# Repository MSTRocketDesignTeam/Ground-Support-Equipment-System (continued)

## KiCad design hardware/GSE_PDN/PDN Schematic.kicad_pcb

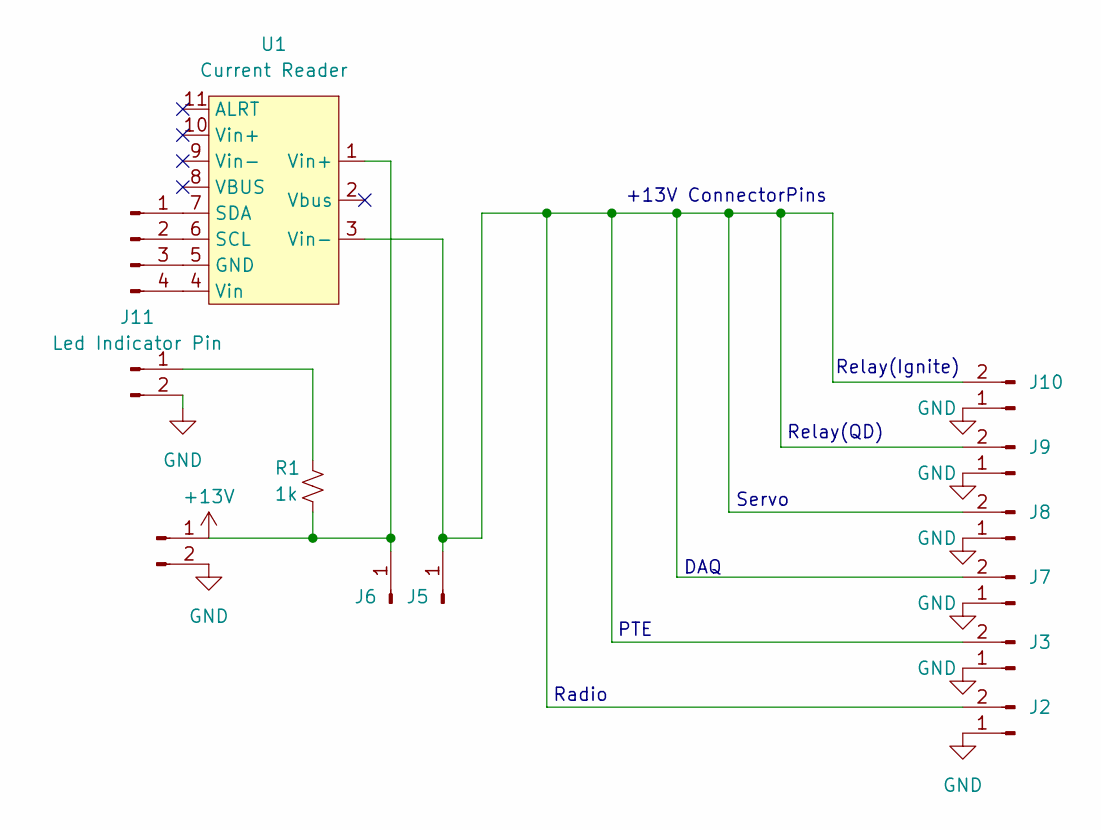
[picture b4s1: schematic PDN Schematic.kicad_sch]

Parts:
J1, J2, J3, J7, J8, J9, J10: Conn_01x02_Pin; PinHeader_1x02_P2.54mm_Vertical
J4: Conn_01x04_Pin; PinHeader_1x04_P2.54mm_Vertical
J5, J6: Conn_01x01_Pin; PinHeader_1x01_P2.54mm_Vertical
J11: Led Indicator Pin; PinHeader_1x02_P2.54mm_Vertical
R1: 1k; R_1206_3216Metric
U1: Current Reader; INA238_MODULE

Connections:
+13V: J1.1, J6.1, R1.2, U1.1 (Vin+)
GND: J1.2, J2.1, J3.1, J7.1, J8.1, J9.1, J10.1, J11.2
unnamed: J4.1, U1.7 (SDA)
unnamed: J4.2, U1.6 (SCL)
unnamed: J4.3, U1.5 (GND)
unnamed: J4.4, U1.4 (Vin)
unnamed: J2.2, J3.2, J5.1, J7.2, J8.2, J9.2, J10.2, U1.3 (Vin-)
unnamed: J11.1, R1.1

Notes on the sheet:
Relay(Ignite)
Servo
Radio
Relay(QD)
+13V ConnectorPins
DAQ
PTE

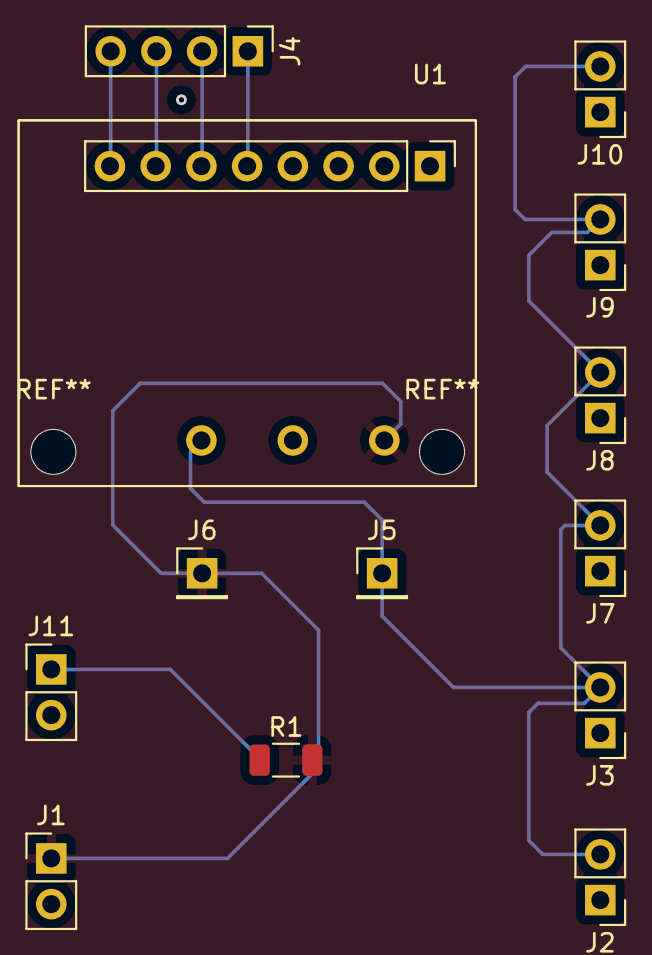
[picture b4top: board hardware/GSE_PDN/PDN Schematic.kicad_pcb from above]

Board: 2 copper layers, 13 parts (0 on the bottom side), 8 nets.

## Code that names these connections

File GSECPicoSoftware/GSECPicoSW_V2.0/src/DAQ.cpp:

#include "DAQ.h"

// Pin Assignments
int MCP3564_MISO_PIN = 4;   
int MCP3564_MOSI_PIN = 7;
int MCP3564_SCK_PIN = 6;
int MCP3564_CS_PIN = 5;

int TCIC_MISO_PIN  = 8;
int TCIC_SCK_PIN   = 10;
int TC1_CS_PIN     = 9;   // GN2 TC
int TC2_CS_PIN     = 13;   // Internal TC
int TC3_CS_PIN     = 12;   // N2O TC

// MAX31855 TCIC SPI Settings
SPISettings tcSPISettings(4000000, MSBFIRST, SPI_MODE0);

// MCP3564 ADC Settings
SPISettings adcSPISettings(5000000, MSBFIRST, SPI_MODE0);         // SPI Bus is 4MHz, MSb-First, Mode 0,0.  


// -------------------------
// MAX31855 read (SPI1)
// -------------------------
uint32_t read_MAX31855(int csPin) {
    SPI1.beginTransaction(tcSPISettings);
    digitalWrite(csPin, LOW);

    uint32_t raw = 0;
    uint8_t rawH = SPI1.transfer(0x00);
    uint8_t rawL = SPI1.transfer(0x00);

    digitalWrite(csPin, HIGH);
    SPI1.endTransaction();

    raw = ((uint32_t)rawH << 8) | rawL;
    raw = raw >> 2;

    return raw;
}

// -------------------------
// MCP3564 read (SPI0)
// -------------------------
uint32_t analog_read_MCP3564_mux_chan(int csPin, int posMuxChanByte, int negMuxChanByte) {
    

    SPI.beginTransaction(adcSPISettings);
    _u32data_t CONV_DATA; 
    CONV_DATA.DWORD = 0x00000000;
    _u16data_t ADC_CRC;
    ADC_CRC.WORD = 0x0000;
    uint64_t CALC_CRC = 0x000000000000;

    if(CONV_START(posMuxChanByte | negMuxChanByte) == 0x13) {     // Convert posMuxChanByte(+) and negMuxChanByte(-) channel ("single ended" reading) and check Data-Ready(DR) Bit of STATUS Byte.               
        CONV_DATA.DWORD = SPI_RD(_ADCDATA_, ADC_CRC, CALC_CRC);      // Read Signal Conversion data.
    }  // ADC Readings will be uncharacteristically perfectly stable at zero if there is no valid reading of the analog channel

    SPI.endTransaction();

    // Masking the "insignificant" status bits and padding, and returning only the lowest 24 bits (the actual ADC conversion reading)
    return (CONV_DATA.DWORD & 0x00FFFFFF);   // Returns in uint_32_t format, but directly in byte form
}

// -------------------------
// Initialization
// -------------------------
void init_DAQ() {
    // Chip Select Pins
    pinMode(MCP3564_CS_PIN, OUTPUT);
    pinMode(TC1_CS_PIN, OUTPUT);
    pinMode(TC2_CS_PIN, OUTPUT);
    pinMode(TC3_CS_PIN, OUTPUT);

    digitalWrite(MCP3564_CS_PIN, HIGH);
    digitalWrite(TC1_CS_PIN, HIGH);
    digitalWrite(TC2_CS_PIN, HIGH);
    digitalWrite(TC3_CS_PIN, HIGH);

    // SPI0 → MCP3564
    SPI.setRX(MCP3564_MISO_PIN);   // MISO
    SPI.setTX(MCP3564_MOSI_PIN);   // MOSI
    SPI.setSCK(MCP3564_SCK_PIN);   // SCK
    SPI.setCS(MCP3564_CS_PIN);     // CS 
    SPI.begin();
    SPI.beginTransaction(adcSPISettings);
    // Configure ADC
    MCP3x6x_CONFIG();    // MCP3564 Register Configuration.
    SPI.endTransaction();
    delayMicroseconds(10);         // Theoretical min is 256 AMCK cycles (256us if SCK is at 1 MHz??) (see T_ADC_SETUP in datasheet for MCP3564)

    // SPI1 → MAX31855
    SPI1.setRX(TCIC_MISO_PIN);     // MISO
    SPI1.setSCK(TCIC_SCK_PIN);     // SCK
    SPI1.begin();    
}

// -------------------------
// High‑level DAQ read function (pass by reference parameters so that they can be modified)
// -------------------------
void read_DAQ_module(
    volatile uint32_t &AI0Reading,
    volatile uint32_t &AI1Reading,
    volatile uint32_t &AI2Reading,
    volatile uint32_t &AI3Reading,
    volatile uint32_t &TC1Reading,
    volatile uint32_t &TC2Reading,
    volatile uint32_t &TC3Reading
) {
    // Read ADC channels
    AI0Reading = analog_read_MCP3564_mux_chan(MCP3564_CS_PIN, MUX_VINP_CH0, MUX_VINN_AGND);
    AI1Reading = analog_read_MCP3564_mux_chan(MCP3564_CS_PIN, MUX_VINP_CH1, MUX_VINN_AGND);
    AI2Reading = analog_read_MCP3564_mux_chan(MCP3564_CS_PIN, MUX_VINP_CH2, MUX_VINN_AGND);
    AI3Reading = analog_read_MCP3564_mux_chan(MCP3564_CS_PIN, MUX_VINP_CH3, MUX_VINN_AGND);
    
    // Read thermocouples
    TC1Reading = read_MAX31855(TC1_CS_PIN);
    TC2Reading = read_MAX31855(TC2_CS_PIN);
    TC3Reading = read_MAX31855(TC3_CS_PIN);
}

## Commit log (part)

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2025-02-08 Rakshak Sudhakaran - GUI appearance meets functional requirements for launch
2025-02-08 Updated GSECPicoSW with changes made to cold flow pico sw regarding constant usage
2025-02-12 Rakshak Sudhakaran - Added some more hardware functionality. Need to update pico SW to be compatible with it. Need to find a way to implement hardware functionality with custom toggle and/or rework c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
2025-02-16 Updates to coldFlowTest, need to update positioning of GUI elements in accordance with proper functional HMI design
2025-02-17 Rakshak Sudhakaran - Updated cold flow SW to allow control for 2 servos and user input run time
2025-02-17 Updated GSEC Pico Cold Flow SW for operation of two servos
2025-03-06 Updated control angle definition of the servos
2025-03-06 Updated servo control angle definitions
2025-09-26 GSE PDN Files
2025-10-03 Close to finalized PCB Layout for GSE PDN
2025-10-04 V1 of schematic
2025-10-17 Hopefully finished schematic
2025-10-17 Imported footprints and libraries
2025-10-17 almost finalized GSE PDN files
2025-10-18 Added footprints and things
2025-10-18 Reuploaded folder
2025-10-19 Extra GSE PDN Board changes
2025-10-24 proper library pathing
2025-10-30 Updated PCB
2025-10-31 Finalish PDN Board
2025-10-31 Hopefully finished PCB
2025-11-06 Generated build files and added component data
2025-11-07 Finished Board
2025-11-14 switched GUI to ttk
2025-11-14 misc commit
2025-11-14 Done
2025-11-14 Ready for final review
2025-11-14 Moved some silkscreen text around
2025-11-15 Swapped positions of radio and INA237 conns for optimized current loop. Swapped 9V LDO to a TI model that supports newer ceramic caps better than the original STM legacy LDO
2025-11-15 resolved single click working on toggles
2025-11-17 Made all buck components on front layer
2025-11-18 Better buck converter positioning with inductor further from analog signals. Improved via stitching and fixed split ground planes somewhat except for Manhattans
2026-01-25 Finished PCBs with production files
2026-03-05 Removed redudancies
2026-03-05 Revert "Rakshak Sudhakaran - Forgot to say that I made the previous commit from SandTRocket regarding updated control logic"
    This reverts commit 2741b68b2c3f01766e19b41769328f6443dd0d30.
2026-03-07 Added windows support
2026-03-07 added stop button
2026-03-07 fixed bugs preventing valves from moving
2026-03-26 Intermediate commit. DAQ code works occasionally (best after 15 mins of power off period!?!?). I think something isn't being configured correctly with the ADC
2026-04-03 Some GUI changes, fixed some race conditions
2026-04-12 Added GSE operation timers and a terminal launch sequence status bar, as well as recursively updating GSECPico status indicators
2026-04-12 Pulled a draft version of SP26SWSandbox into main
2026-04-16 Post hotfire 1 baseline. Launch sequence timing is finalized. Ready to modify for DAQ stuff
2026-04-16 Fixed GUI frame/widget arrangment and made work for center monitor resizing
2026-04-16 Finally merged with SP26SWSandbox
2026-04-26 Made some msg parsing improvements for cold flow testing SW
2026-04-27 Added pico cold flow software to be used by the GSECU. No servo power switch functionality implemented yet
2026-04-30 Pre DAQ functionality implementation baseline
2026-05-09 DAQ functionality working!
2026-05-09 Implemented DAQ functionality on main, need to implement live plotting and accurate engineering value conversions
2026-05-10 Improved data file naming, added sensor calibration framework
2026-05-10 Updated launch sequence logic
2026-05-10 Intermediary commit for debugging serial latency issues
2026-05-13 Fixed latency issue on GSEC Pico SW, but broke LEC transmit :(
2026-05-13 Changed QD and N2O value buttons
2026-05-13 Fixed latency issue and fixed LEC transmit. GSE DAQ and hardware control work seamlessly. Need to implement LEC DAQ now
2026-05-13 LECU DAQ working, but extremely slowly and the readings are off because the bit shift operations are most likely incorrect
2026-05-14 Working LEC and GSE DAQ commit! No latency
2026-05-14 LEC and GSE DAQ working! No latency!
2026-05-18 Added scales for TCs
2026-05-19 Formatting updates. Ready for launch
